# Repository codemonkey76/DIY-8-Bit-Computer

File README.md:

# DIY-8-Bit-Computer

Based off schematics and design of breadboard computer by Ben Eater, available in kit form at: https://eater.net/8bit/kits

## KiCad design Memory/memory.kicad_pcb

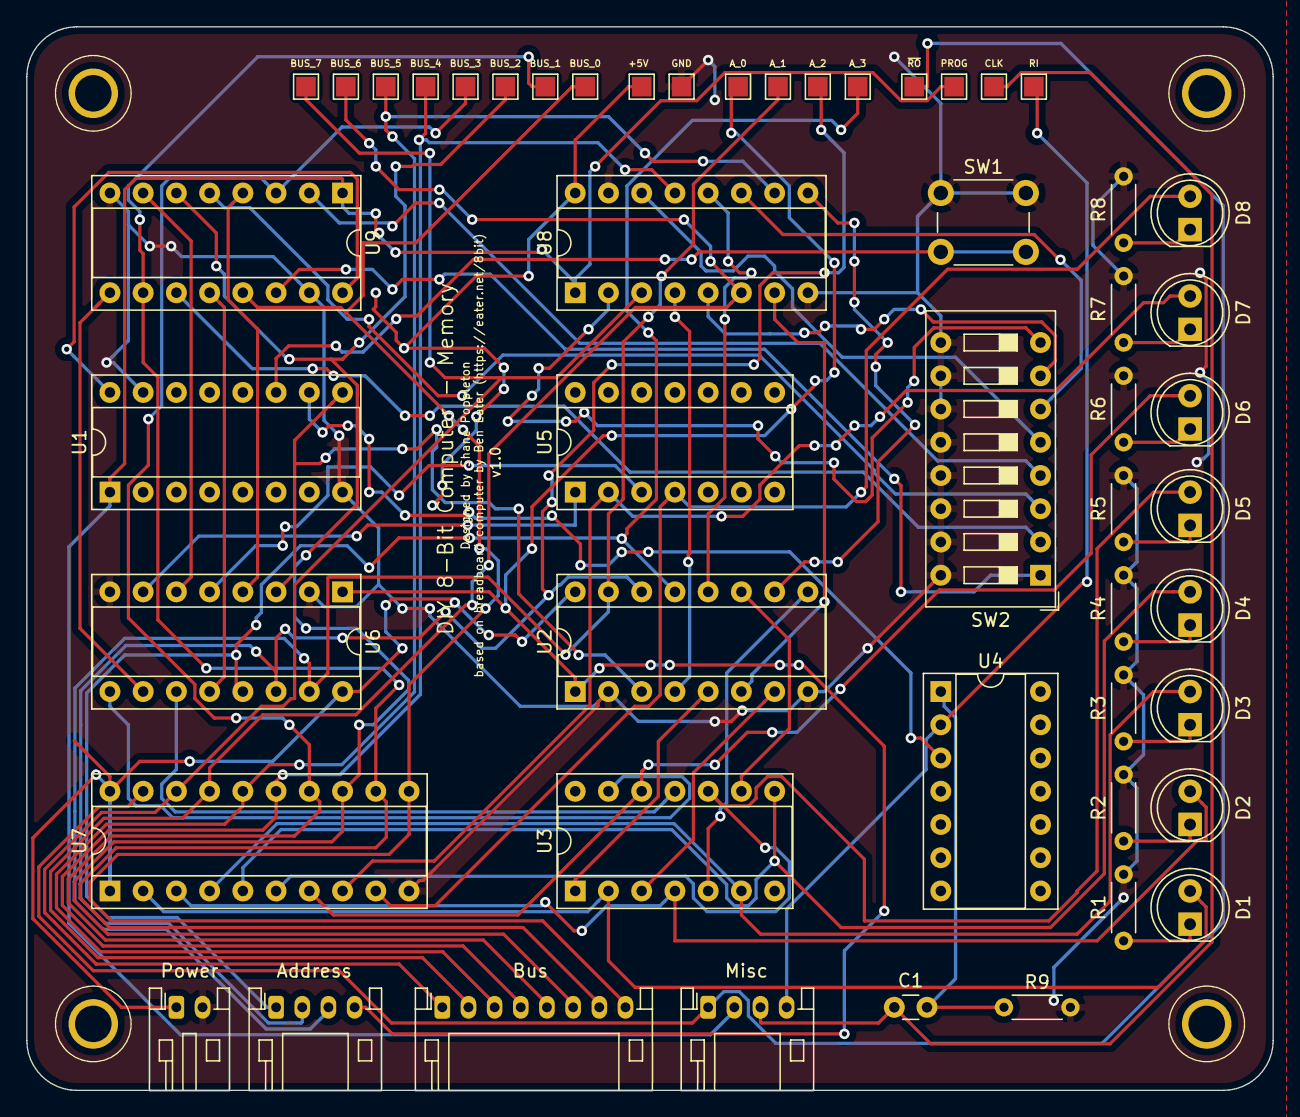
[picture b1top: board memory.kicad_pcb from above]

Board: 2 copper layers, 95.3 x 81.3 mm, 51 parts (0 on the bottom side), 62 nets.

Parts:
C1: 10nF; C_Disc_D3.0mm_W1.6mm_P2.50mm
D1, D2, D3, D4, D5, D6, D7, D8: LED; LED_D5.0mm
J1: Power; JST_PH_S2B-PH-K_1x02_P2.00mm_Horizontal
J2: Misc; JST_PH_S4B-PH-K_1x04_P2.00mm_Horizontal
J3: Address; JST_PH_S4B-PH-K_1x04_P2.00mm_Horizontal
J4: Bus; JST_PH_S8B-PH-K_1x08_P2.00mm_Horizontal
R1, R2, R3, R4, R5, R6, R7, R8: 220R; R_Axial_DIN0204_L3.6mm_D1.6mm_P5.08mm_Horizontal
R9: 1K; R_Axial_DIN0204_L3.6mm_D1.6mm_P5.08mm_Horizontal
SW1: SW_Push; SW_PUSH_6mm_H5mm
SW2: SW_DIP_x08; SW_DIP_SPSTx08_Slide_9.78x22.5mm_W7.62mm_P2.54mm
TP1: +5V; TestPoint_Pad_1.5x1.5mm
TP2: ~RO~; TestPoint_Pad_1.5x1.5mm
TP3: GND; TestPoint_Pad_1.5x1.5mm
TP4: A_3; TestPoint_Pad_1.5x1.5mm
TP5: A_2; TestPoint_Pad_1.5x1.5mm
TP6: A_1; TestPoint_Pad_1.5x1.5mm
TP7: RI; TestPoint_Pad_1.5x1.5mm
TP8: A_0; TestPoint_Pad_1.5x1.5mm
TP9: CLK; TestPoint_Pad_1.5x1.5mm
TP10: PROG; TestPoint_Pad_1.5x1.5mm
TP11: BUS_7; TestPoint_Pad_1.5x1.5mm
TP12: BUS_6; TestPoint_Pad_1.5x1.5mm
TP13: BUS_5; TestPoint_Pad_1.5x1.5mm
TP14: BUS_4; TestPoint_Pad_1.5x1.5mm
TP15: BUS_3; TestPoint_Pad_1.5x1.5mm
TP16: BUS_2; TestPoint_Pad_1.5x1.5mm
TP17: BUS_1; TestPoint_Pad_1.5x1.5mm
TP18: BUS_0; TestPoint_Pad_1.5x1.5mm
U1, U8, U9: 74LS157; DIP-16_W7.62mm_Socket
U2, U6: 74LS189; DIP-16_W7.62mm_Socket
U3, U5: 74LS04; DIP-14_W7.62mm_Socket
U4: 74LS00; DIP-14_W7.62mm_Socket
U7: 74LS245; DIP-20_W7.62mm_Socket

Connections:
+5V: J1.1, TP1.1, U1.16, U2.16, U6.16, U7.1, U7.20, U8.16, U9.16
/A0: J3.4, TP8.1, U2.1, U6.1
/A1: J3.3, TP6.1, U2.15, U6.15
/A2: J3.2, TP5.1, U2.14, U6.14
/A3: J3.1, TP4.1, U2.13, U6.13
/BUS_0: J4.8, TP18.1, U7.11, U9.13
/BUS_1: J4.7, TP17.1, U7.12, U9.10
/BUS_2: J4.6, TP16.1, U7.13, U9.6
/BUS_3: J4.5, TP15.1, U7.14, U9.3
/BUS_4: J4.4, TP14.1, U7.15, U8.13
/BUS_5: J4.3, TP13.1, U7.16, U8.10
/BUS_6: J4.2, TP12.1, U7.17, U8.6
/BUS_7: J4.1, TP11.1, U7.18, U8.3
/CLK: C1.1, J2.3, TP9.1
/PROG: J2.2, TP10.1, U1.1, U8.1, U9.1
/RI: J2.4, TP7.1, U4.2
/~RO~: J2.1, TP2.1, U7.19
GND: J1.2, R1.2, R2.2, R3.2, R4.2, R5.2, R6.2, R7.2, R8.2, R9.2, SW1.1, SW2.9, SW2.10, SW2.11, SW2.12, SW2.13, SW2.14, SW2.15, SW2.16, TP3.1, U1.8, U1.15, U2.2, U2.8, U6.2, U6.8, U7.10, U8.8, U8.15, U9.8, U9.15
unnamed: C1.2, R9.1, U4.1
unnamed: D1.1, R1.1
unnamed: D1.2, U3.2, U7.2
unnamed: D2.1, R2.1
unnamed: D2.2, U3.4, U7.3
unnamed: D3.1, R3.1
unnamed: D3.2, U3.6, U7.4
unnamed: D4.1, R4.1
unnamed: D4.2, U3.8, U7.5
unnamed: D5.1, R5.1
unnamed: D5.2, U3.10, U7.6
unnamed: D6.1, R6.1
unnamed: D6.2, U3.12, U7.7
unnamed: D7.1, R7.1
unnamed: D7.2, U5.2, U7.8
unnamed: D8.1, R8.1
unnamed: D8.2, U5.4, U7.9
unnamed: SW1.2, U1.11
unnamed: SW2.1, U9.14
unnamed: SW2.2, U9.11
unnamed: SW2.3, U9.5
unnamed: SW2.4, U9.2
unnamed: SW2.5, U8.14
unnamed: SW2.6, U8.11
unnamed: SW2.7, U8.5
unnamed: SW2.8, U8.2
unnamed: U1.9, U2.3, U6.3
unnamed: U1.10, U4.3
unnamed: U2.4, U8.4
unnamed: U2.5, U3.1
unnamed: U2.6, U8.7
unnamed: U2.7, U3.3
unnamed: U2.9, U3.5
unnamed: U2.10, U8.9
unnamed: U2.11, U3.9
unnamed: U2.12, U8.12
unnamed: U3.11, U6.11
unnamed: U3.13, U6.9
unnamed: U5.1, U6.7
unnamed: U5.3, U6.5
unnamed: U6.4, U9.4
unnamed: U6.6, U9.7
unnamed: U6.10, U9.9
unnamed: U6.12, U9.12

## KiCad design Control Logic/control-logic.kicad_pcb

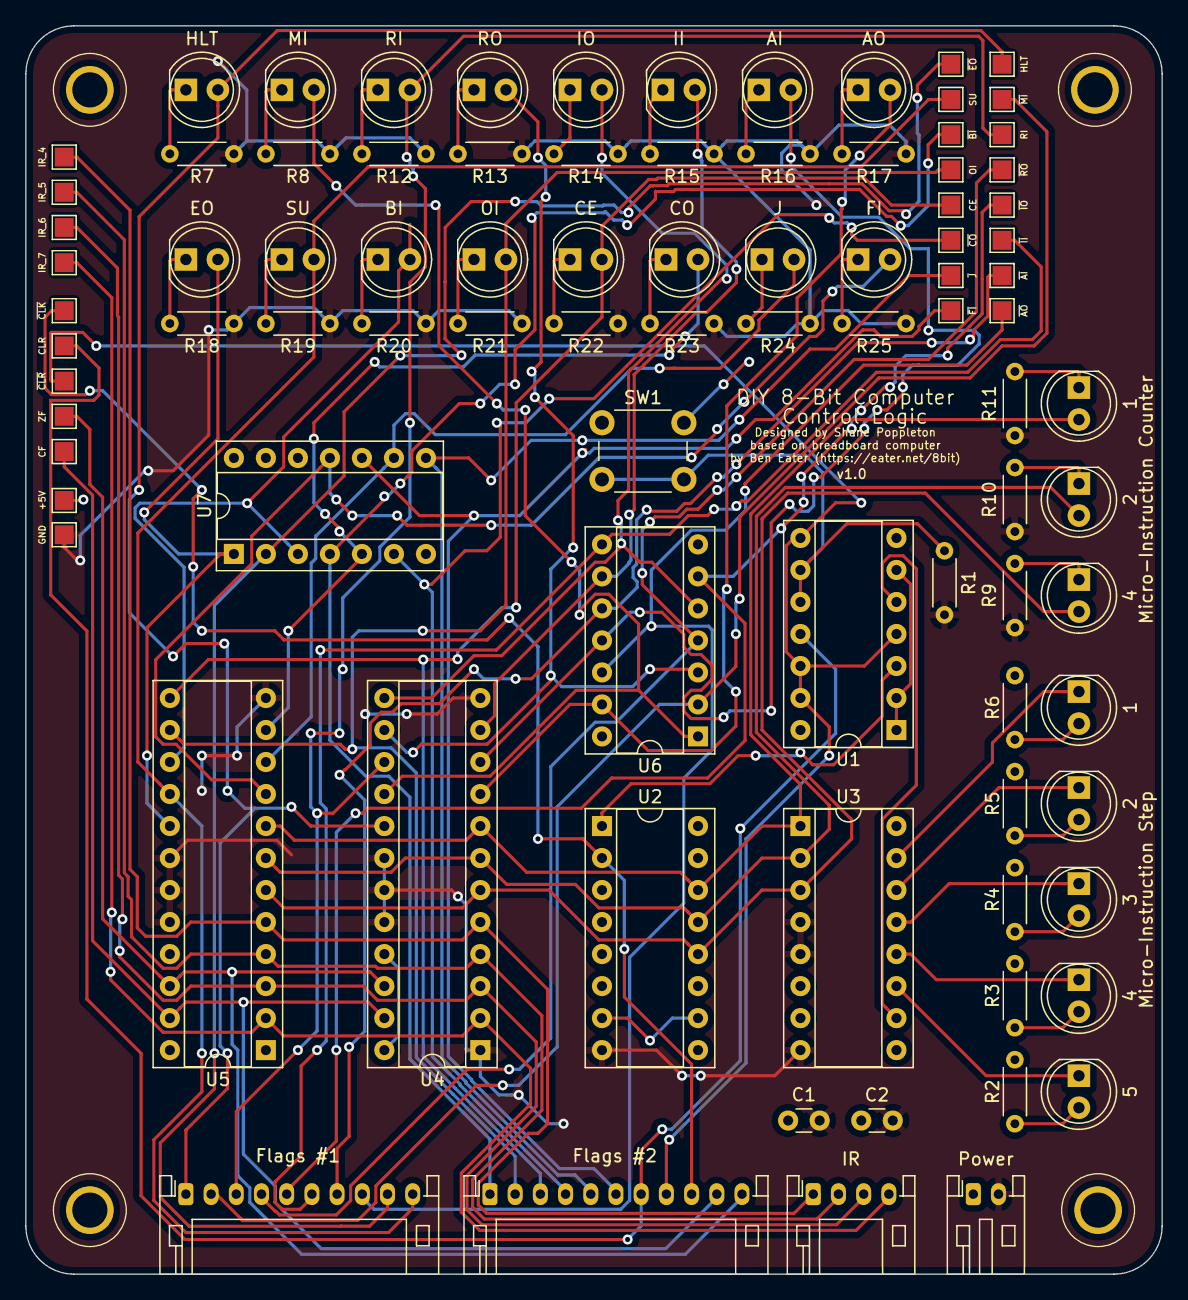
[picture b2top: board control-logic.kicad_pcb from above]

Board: 2 copper layers, 90.2 x 99.1 mm, 90 parts (0 on the bottom side), 74 nets.

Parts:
C1, C2: 100nF; C_Disc_D3.0mm_W1.6mm_P2.50mm
D1: 5; LED_D5.0mm
D2, D10: 4; LED_D5.0mm
D3: 3; LED_D5.0mm
D4, D11: 2; LED_D5.0mm
D5, D12: 1; LED_D5.0mm
D6: HLT; LED_D5.0mm
D7: MI; LED_D5.0mm
D8: RI; LED_D5.0mm
D9: RO; LED_D5.0mm
D13: IO; LED_D5.0mm
D14: II; LED_D5.0mm
D15: AI; LED_D5.0mm
D16: AO; LED_D5.0mm
D17: EO; LED_D5.0mm
D18: SU; LED_D5.0mm
D19: BI; LED_D5.0mm
D20: OI; LED_D5.0mm
D21: CE; LED_D5.0mm
D22: CO; LED_D5.0mm
D23: J; LED_D5.0mm
D24: FI; LED_D5.0mm
J1: Power; JST_PH_S2B-PH-K_1x02_P2.00mm_Horizontal
J2: IR; JST_PH_S4B-PH-K_1x04_P2.00mm_Horizontal
J3: Flags #2; JST_PH_S11B-PH-K_1x11_P2.00mm_Horizontal
J4: Flags #1; JST_PH_S10B-PH-K_1x10_P2.00mm_Horizontal
R1: 1K; R_Axial_DIN0204_L3.6mm_D1.6mm_P5.08mm_Horizontal
R2, R3, R4, R5, R6, R7, R8, R9, R10, R11, R12, R13, R14, R15, R16, R17, R18, R19, R20, R21, R22, R23, R24, R25: 220R; R_Axial_DIN0204_L3.6mm_D1.6mm_P5.08mm_Horizontal
SW1: SW_Push; SW_PUSH_6mm_H5mm
TP1: +5V; TestPoint_Pad_1.5x1.5mm
TP2: GND; TestPoint_Pad_1.5x1.5mm
TP3: ~CLR~; TestPoint_Pad_1.5x1.5mm
TP4: CLR; TestPoint_Pad_1.5x1.5mm
TP5: ~CLK~; TestPoint_Pad_1.5x1.5mm
TP6: IR_4; TestPoint_Pad_1.5x1.5mm
TP7: IR_5; TestPoint_Pad_1.5x1.5mm
TP8: IR_6; TestPoint_Pad_1.5x1.5mm
TP9: IR_7; TestPoint_Pad_1.5x1.5mm
TP10: CF; TestPoint_Pad_1.5x1.5mm
TP11: ZF; TestPoint_Pad_1.5x1.5mm
TP12: HLT; TestPoint_Pad_1.5x1.5mm
TP13: ~II~; TestPoint_Pad_1.5x1.5mm
TP14: ~MI~; TestPoint_Pad_1.5x1.5mm
TP15: ~AI~; TestPoint_Pad_1.5x1.5mm
TP16: RI; TestPoint_Pad_1.5x1.5mm
TP17: ~AO~; TestPoint_Pad_1.5x1.5mm
TP18: ~RO~; TestPoint_Pad_1.5x1.5mm
TP19: ~IO~; TestPoint_Pad_1.5x1.5mm
TP20: ~EO~; TestPoint_Pad_1.5x1.5mm
TP21: OI; TestPoint_Pad_1.5x1.5mm
TP22: ~CO~; TestPoint_Pad_1.5x1.5mm
TP23: SU; TestPoint_Pad_1.5x1.5mm
TP24: ~J~; TestPoint_Pad_1.5x1.5mm
TP25: CE; TestPoint_Pad_1.5x1.5mm
TP26: ~FI~; TestPoint_Pad_1.5x1.5mm
TP27: ~BI~; TestPoint_Pad_1.5x1.5mm
U1: 74LS00; DIP-14_W7.62mm_Socket
U2: 74LS161; DIP-16_W7.62mm_Socket
U3: 74LS138; DIP-16_W7.62mm_Socket
U4, U5: 24C16; DIP-24_W7.62mm_Socket
U6, U7: 74LS04; DIP-14_W7.62mm_Socket

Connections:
+5V: C1.1, C2.1, J1.1, R2.1, R3.1, R4.1, R5.1, R6.1, SW1.1, TP1.1, U2.7, U2.9, U2.10, U2.16, U3.6, U3.16, U4.21, U4.24, U5.1, U5.21, U5.24
/CE: D21.2, J3.3, TP25.1, U5.13
/HLT: D6.2, J4.1, TP12.1, U4.17
/IR_4: J2.1, TP6.1, U4.5, U5.5
/IR_5: J2.2, TP7.1, U4.4, U5.4
/IR_6: J2.3, TP8.1, U4.3, U5.3
/IR_7: J2.4, TP9.1, U4.2, U5.2
/OI: D20.2, J3.2, TP21.1, U5.14
/RI: D8.2, J4.3, TP16.1, U4.15
/SU: D18.2, J4.10, TP23.1, U5.16
/~AI~: J4.7, TP15.1, U6.10
/~AO~: J4.8, TP17.1, U6.12
/~BI~: J3.1, TP27.1, U7.4
/~CO~: J3.4, TP22.1, U7.6
/~EO~: J4.9, TP20.1, U7.2
/~FI~: J3.6, TP26.1, U7.10
/~II~: J4.6, TP13.1, U6.8
/~IO~: J4.5, TP19.1, U6.6
/~J~: J3.5, TP24.1, U7.8
/~MI~: J4.2, TP14.1, U6.2
/~RO~: J4.4, TP18.1, U6.4
CF: J3.10, TP10.1, U4.23, U5.23
CLR: J3.7, TP4.1, U1.11
GND: C1.2, C2.2, J1.2, R1.2, R7.2, R8.2, R9.2, R10.2, R11.2, R12.2, R13.2, R14.2, R15.2, R16.2, R17.2, R18.2, R19.2, R20.2, R21.2, R22.2, R23.2, R24.2, R25.2, TP2.1, U2.8, U3.4, U3.5, U3.8, U4.1, U4.12, U4.18, U4.19, U4.20, U5.12, U5.18, U5.19, U5.20
unnamed: D1.1, U3.11
unnamed: D1.2, R2.2
unnamed: D2.1, U3.12
unnamed: D2.2, R3.2
unnamed: D3.1, U3.13
unnamed: D3.2, R4.2
unnamed: D4.1, U3.14
unnamed: D4.2, R5.2
unnamed: D5.1, U3.15
unnamed: D5.2, R6.2
unnamed: D6.1, R7.1
unnamed: D7.1, R8.1
unnamed: D7.2, U4.16, U6.1
unnamed: D8.1, R12.1
unnamed: D9.1, R13.1
unnamed: D9.2, U4.14, U6.3
unnamed: D10.1, R9.1
unnamed: D10.2, U2.12, U3.3, U4.6, U5.6
unnamed: D11.1, R10.1
unnamed: D11.2, U2.13, U3.2, U4.7, U5.7
unnamed: D12.1, R11.1
unnamed: D12.2, U2.14, U3.1, U4.8, U5.8
unnamed: D13.1, R14.1
unnamed: D13.2, U4.13, U6.5
unnamed: D14.1, R15.1
unnamed: D14.2, U4.11, U6.9
unnamed: D15.1, R16.1
unnamed: D15.2, U4.10, U6.11
unnamed: D16.1, R17.1
unnamed: D16.2, U4.9, U6.13
unnamed: D17.1, R18.1
unnamed: D17.2, U5.17, U7.1
unnamed: D18.1, R19.1
unnamed: D19.1, R20.1
unnamed: D19.2, U5.15, U7.3
unnamed: D20.1, R21.1
unnamed: D21.1, R22.1
unnamed: D22.1, R23.1
unnamed: D22.2, U5.11, U7.5
unnamed: D23.1, R24.1
unnamed: D23.2, U5.10, U7.9
unnamed: D24.1, R25.1
unnamed: D24.2, U5.9, U7.11
unnamed: R1.1, SW1.2, U1.9, U1.10
unnamed: U1.1, U1.2, U1.6
unnamed: U1.3, U2.1
unnamed: U1.5, U3.10
ZF: J3.11, TP11.1, U4.22, U5.22
~CLK~: J3.9, TP5.1, U2.2
~CLR~: J3.8, TP3.1, U1.4, U1.8, U1.12, U1.13

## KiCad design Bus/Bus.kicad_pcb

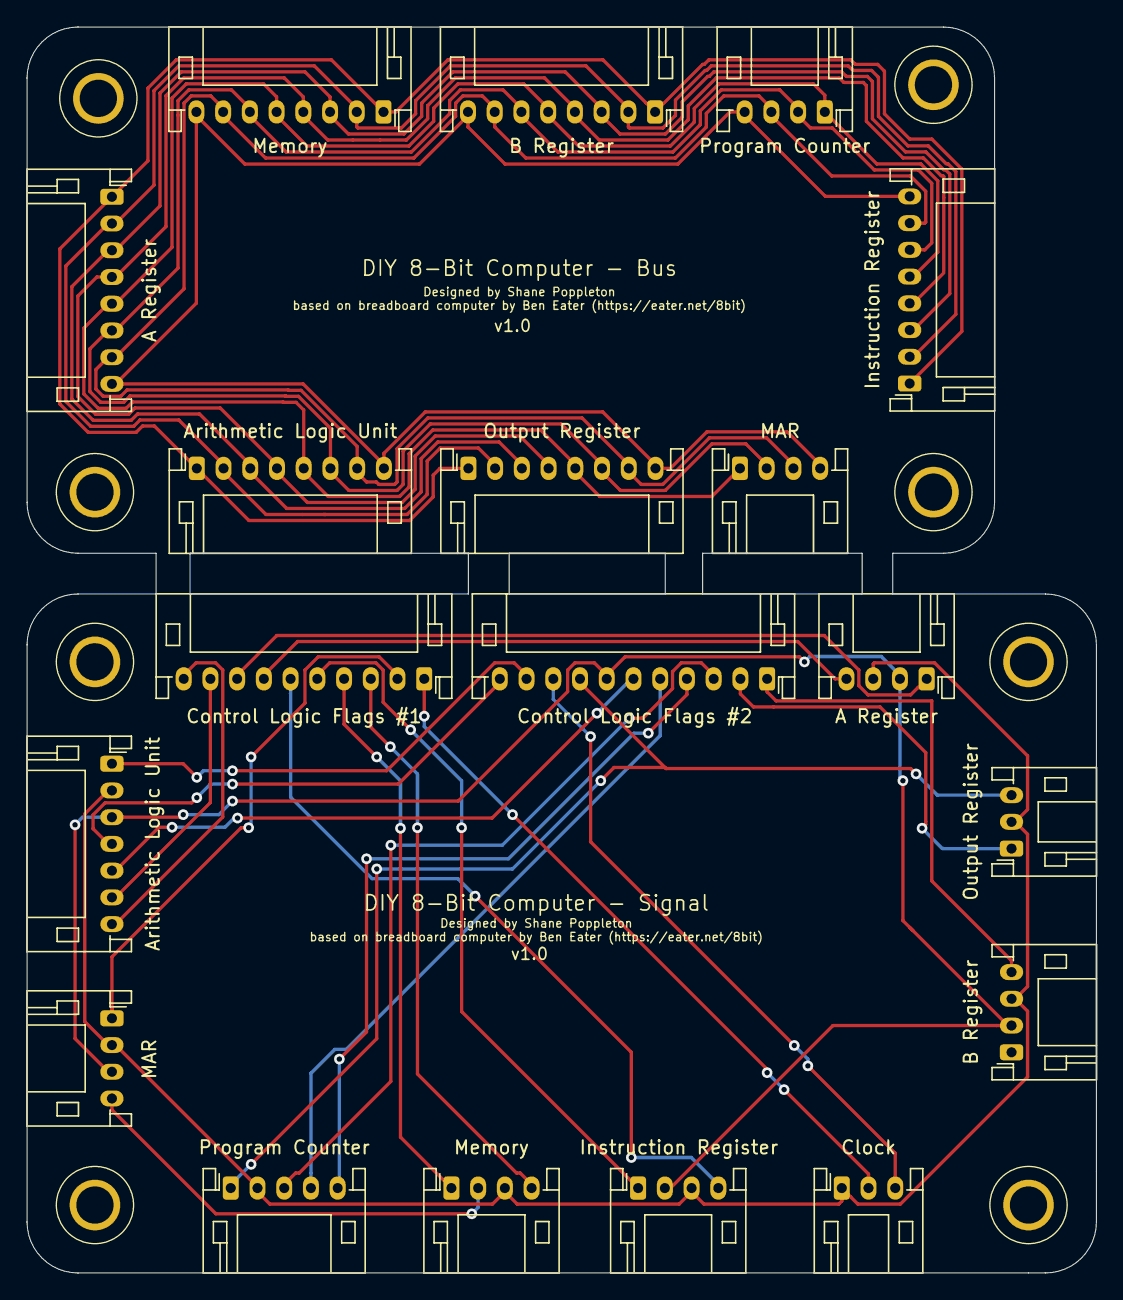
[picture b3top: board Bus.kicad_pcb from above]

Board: 2 copper layers, 80.0 x 93.2 mm, 19 parts (0 on the bottom side), 31 nets.

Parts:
J1: Clock; JST_PH_S3B-PH-K_1x03_P2.00mm_Horizontal
J2: Control Logic Flags #1; JST_PH_S10B-PH-K_1x10_P2.00mm_Horizontal
J3: Output Register; JST_PH_S8B-PH-K_1x08_P2.00mm_Horizontal
J5: Output Register; JST_PH_S3B-PH-K_1x03_P2.00mm_Horizontal
J8: Instruction Register; JST_PH_S8B-PH-K_1x08_P2.00mm_Horizontal
J9: Control Logic Flags #2; JST_PH_S11B-PH-K_1x11_P2.00mm_Horizontal
J12: Instruction Register; JST_PH_S4B-PH-K_1x04_P2.00mm_Horizontal
J13: A Register; JST_PH_S8B-PH-K_1x08_P2.00mm_Horizontal
J17: A Register; JST_PH_S4B-PH-K_1x04_P2.00mm_Horizontal
J18, J19: MAR; JST_PH_S4B-PH-K_1x04_P2.00mm_Horizontal
J20: B Register; JST_PH_S8B-PH-K_1x08_P2.00mm_Horizontal
J25: B Register; JST_PH_S4B-PH-K_1x04_P2.00mm_Horizontal
J26: Memory; JST_PH_S8B-PH-K_1x08_P2.00mm_Horizontal
J29: Memory; JST_PH_S4B-PH-K_1x04_P2.00mm_Horizontal
J30: Arithmetic Logic Unit; JST_PH_S7B-PH-K_1x07_P2.00mm_Horizontal
J31: Arithmetic Logic Unit; JST_PH_S8B-PH-K_1x08_P2.00mm_Horizontal
J32: Program Counter; JST_PH_S4B-PH-K_1x04_P2.00mm_Horizontal
J36: Program Counter; JST_PH_S5B-PH-K_1x05_P2.00mm_Horizontal

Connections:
BUS_0: J3.8, J8.8, J13.8, J19.4, J20.8, J26.8, J31.8, J32.4
BUS_1: J3.7, J8.7, J13.7, J19.3, J20.7, J26.7, J31.7, J32.3
BUS_2: J3.6, J8.6, J13.6, J19.2, J20.6, J26.6, J31.6, J32.2
BUS_3: J3.5, J8.5, J13.5, J19.1, J20.5, J26.5, J31.5, J32.1
BUS_4: J3.4, J8.4, J13.4, J20.4, J26.4, J31.4
BUS_5: J3.3, J8.3, J13.3, J20.3, J26.3, J31.3
BUS_6: J3.2, J8.2, J13.2, J20.2, J26.2, J31.2
BUS_7: J3.1, J8.1, J13.1, J20.1, J26.1, J31.1
CE: J9.3, J36.3
CF: J9.10, J30.1
CLK: J1.1, J5.2, J12.3, J17.3, J18.2, J25.3, J29.3, J30.2, J36.2
CLR: J9.7, J12.2, J17.2, J18.3, J25.2, J30.3
HLT: J1.2, J2.1
OI: J5.1, J9.2
PROG: J18.4, J29.2
RI: J2.3, J29.4
SU: J2.10, J30.7
ZF: J9.11, J30.4
~AI~: J2.7, J17.4
~AO~: J2.8, J17.1
~BI~: J9.1, J25.4
~CLK~: J1.3, J9.9
~CLR~: J5.3, J9.8, J36.1
~CO~: J9.4, J36.5
~EO~: J2.9, J30.6
~FI~: J9.6, J30.5
~II~: J2.6, J12.4
~IO~: J2.5, J12.1
~J~: J9.5, J36.4
~MI~: J2.2, J18.1
~RO~: J2.4, J29.1

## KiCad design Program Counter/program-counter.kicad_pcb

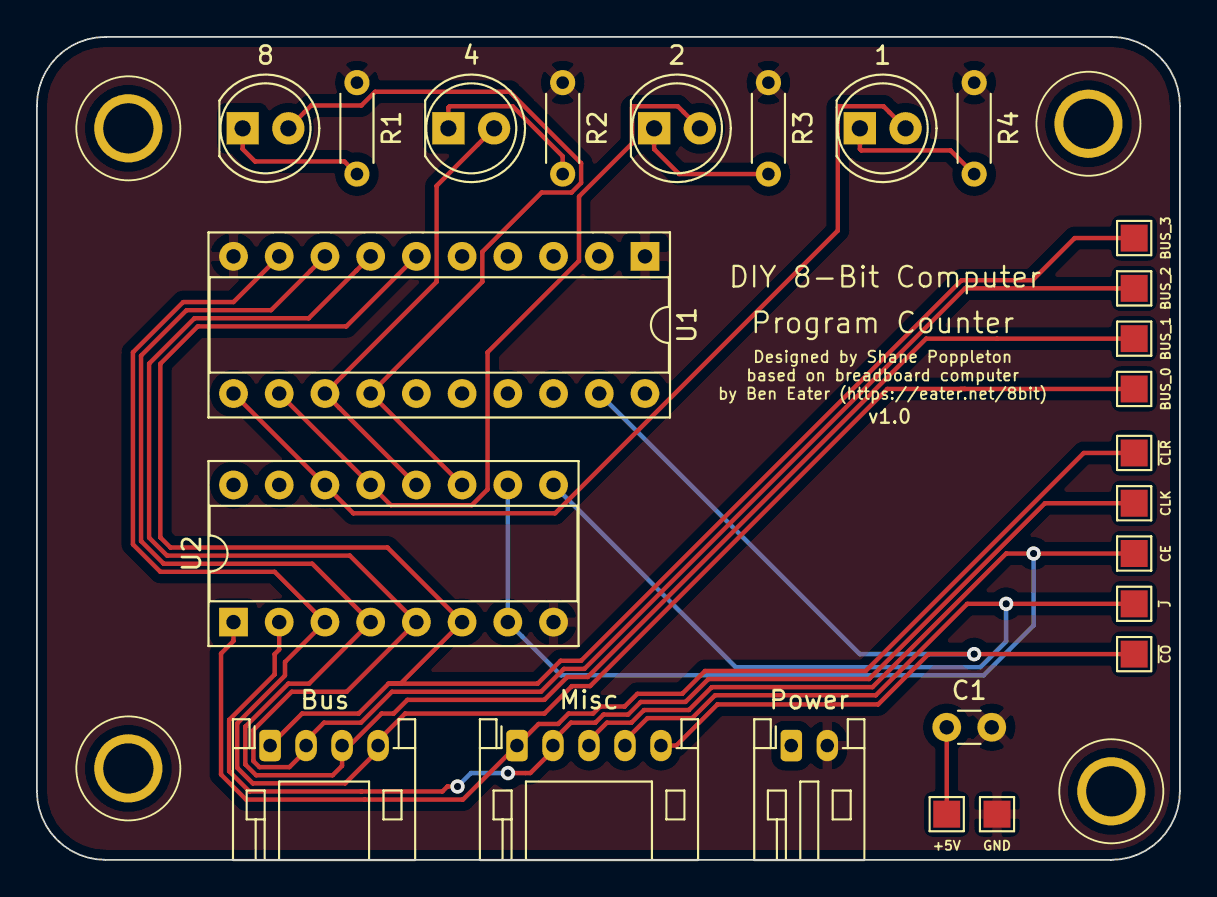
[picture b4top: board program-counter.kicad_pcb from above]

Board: 2 copper layers, 63.5 x 45.7 mm, 25 parts (0 on the bottom side), 19 nets.

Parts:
C1: 100nF; C_Disc_D3.0mm_W1.6mm_P2.50mm
D1: 8; LED_D5.0mm
D2: 4; LED_D5.0mm
D3: 2; LED_D5.0mm
D4: 1; LED_D5.0mm
J1: Misc; JST_PH_S5B-PH-K_1x05_P2.00mm_Horizontal
J2: Bus; JST_PH_S4B-PH-K_1x04_P2.00mm_Horizontal
J3: Power; JST_PH_S2B-PH-K_1x02_P2.00mm_Horizontal
R1, R2, R3, R4: 220R; R_Axial_DIN0204_L3.6mm_D1.6mm_P5.08mm_Horizontal
TP1: ~CO~; TestPoint_Pad_1.5x1.5mm
TP2: ~CLR~; TestPoint_Pad_1.5x1.5mm
TP3: CLK; TestPoint_Pad_1.5x1.5mm
TP4: ~J~; TestPoint_Pad_1.5x1.5mm
TP5: CE; TestPoint_Pad_1.5x1.5mm
TP6: BUS_2; TestPoint_Pad_1.5x1.5mm
TP7: BUS_0; TestPoint_Pad_1.5x1.5mm
TP8: BUS_1; TestPoint_Pad_1.5x1.5mm
TP9: BUS_3; TestPoint_Pad_1.5x1.5mm
TP10: GND; TestPoint_Pad_1.5x1.5mm
TP11: +5V; TestPoint_Pad_1.5x1.5mm
U1: 74LS245; DIP-20_W7.62mm_Socket
U2: 74LS161; DIP-16_W7.62mm_Socket

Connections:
+5V: C1.1, J3.1, TP11.1, U1.20, U2.16
/BUS_0: J2.4, TP7.1, U1.9, U2.3
/BUS_1: J2.3, TP8.1, U1.8, U2.4
/BUS_2: J2.2, TP6.1, U1.7, U2.5
/BUS_3: J2.1, TP9.1, U1.6, U2.6
/CE: J1.3, TP5.1, U2.7, U2.10
/CLK: J1.2, TP3.1, U2.2
/~CLR~: J1.1, TP2.1, U2.1
/~CO~: J1.5, TP1.1, U1.19
/~J~: J1.4, TP4.1, U2.9
GND: C1.2, J3.2, R1.1, R2.1, R3.1, R4.1, TP10.1, U1.1, U1.10, U2.8
unnamed: D1.1, R1.2
unnamed: D1.2, U1.14, U2.11
unnamed: D2.1, R2.2
unnamed: D2.2, U1.13, U2.12
unnamed: D3.1, R3.2
unnamed: D3.2, U1.12, U2.13
unnamed: D4.1, R4.2
unnamed: D4.2, U1.11, U2.14

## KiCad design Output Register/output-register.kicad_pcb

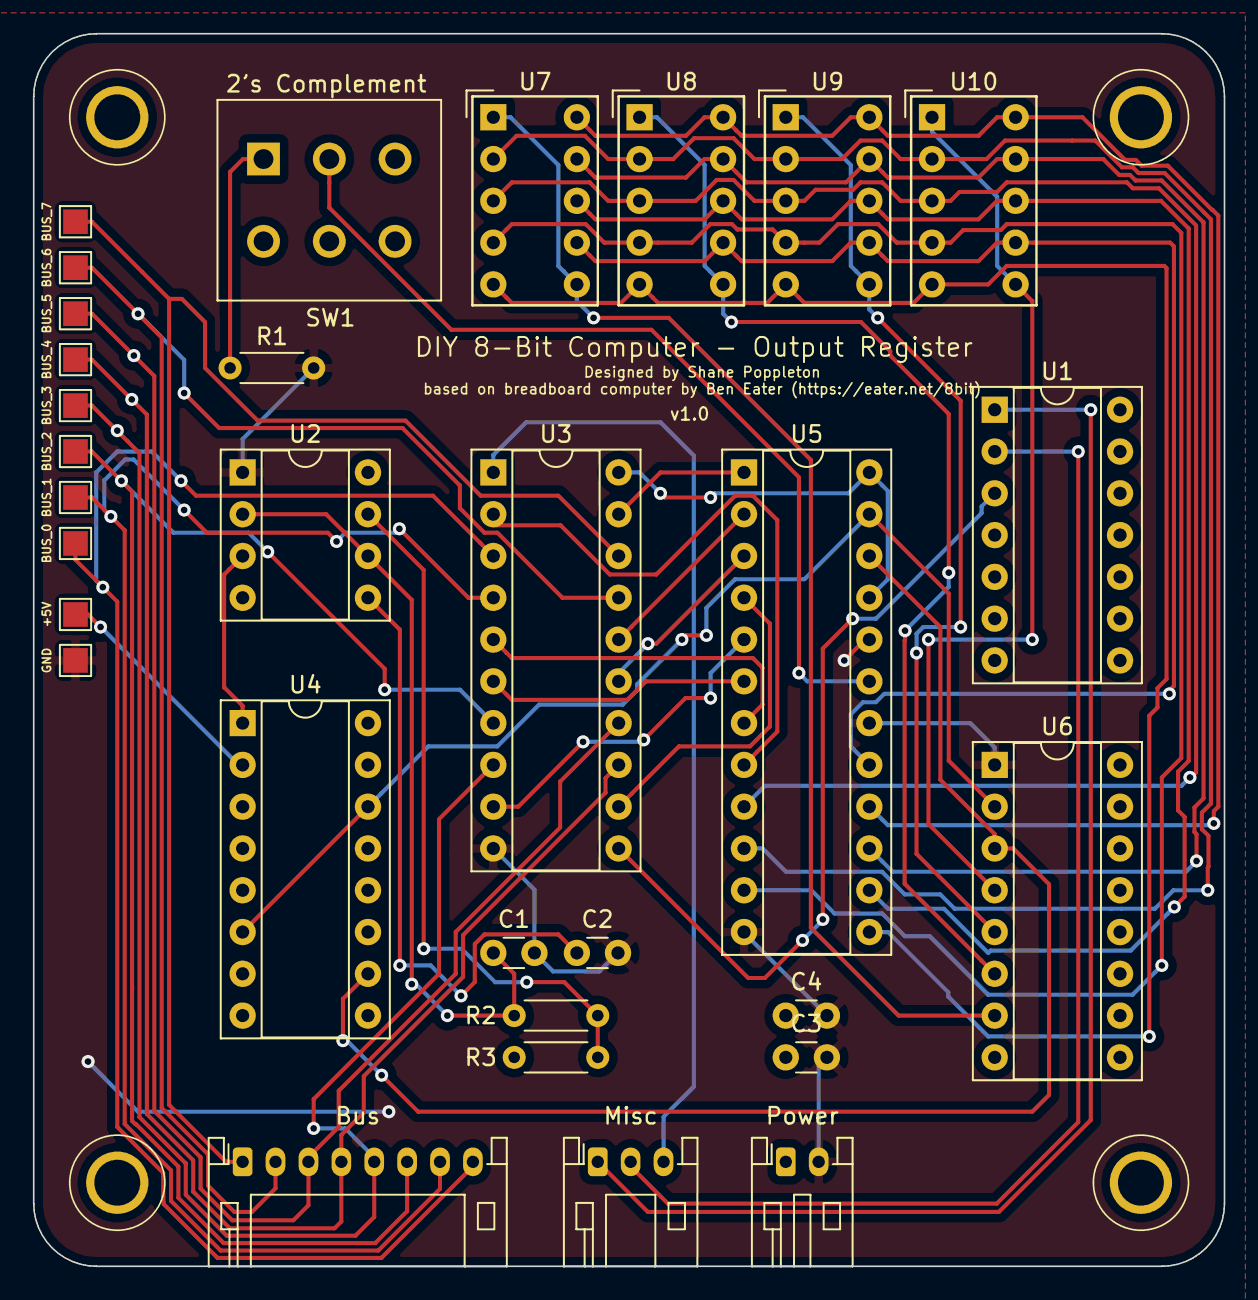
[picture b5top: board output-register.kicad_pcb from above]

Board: 2 copper layers, 72.4 x 74.9 mm, 31 parts (0 on the bottom side), 42 nets.

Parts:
C1, C2: 10nF; C_Disc_D3.0mm_W1.6mm_P2.50mm
C3, C4: 100nF; C_Disc_D3.0mm_W1.6mm_P2.50mm
J1: Bus; JST_PH_S8B-PH-K_1x08_P2.00mm_Horizontal
J2: Power; JST_PH_S2B-PH-K_1x02_P2.00mm_Horizontal
J3: Misc; JST_PH_S3B-PH-K_1x03_P2.00mm_Horizontal
R1: 10K; R_Axial_DIN0204_L3.6mm_D1.6mm_P5.08mm_Horizontal
R2: 100K; R_Axial_DIN0204_L3.6mm_D1.6mm_P5.08mm_Horizontal
R3: 1K; R_Axial_DIN0204_L3.6mm_D1.6mm_P5.08mm_Horizontal
SW1: Negative; SW_PUSH_E-Switch_FS5700DP_DPDT
TP1: BUS_0; TestPoint_Pad_1.5x1.5mm
TP2: BUS_1; TestPoint_Pad_1.5x1.5mm
TP3: BUS_2; TestPoint_Pad_1.5x1.5mm
TP4: BUS_3; TestPoint_Pad_1.5x1.5mm
TP5: BUS_4; TestPoint_Pad_1.5x1.5mm
TP6: BUS_5; TestPoint_Pad_1.5x1.5mm
TP7: BUS_6; TestPoint_Pad_1.5x1.5mm
TP8: BUS_7; TestPoint_Pad_1.5x1.5mm
TP9: +5V; TestPoint_Pad_1.5x1.5mm
TP10: GND; TestPoint_Pad_1.5x1.5mm
U1: 74LS08; DIP-14_W7.62mm_Socket
U2: LM555; DIP-8_W7.62mm_Socket
U3: 74LS273; DIP-20_W7.62mm_Socket
U4: 74LS76; DIP-16_W7.62mm_Socket
U5: 24C16; DIP-24_W7.62mm_Socket
U6: 74LS139; DIP-16_W7.62mm_Socket
U7, U8, U9, U10: HDSP-7403; HDSP-7401

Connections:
+5V: C3.1, C4.1, J2.1, R3.1, SW1.3, TP9.1, U2.8, U3.20, U4.2, U4.3, U4.4, U4.7, U4.8, U4.9, U4.12, U4.16, U5.21, U5.24
/BUS_0: J1.8, TP1.1, U3.3
/BUS_1: J1.7, TP2.1, U3.4
/BUS_2: J1.6, TP3.1, U3.7
/BUS_3: J1.5, TP4.1, U3.8
/BUS_4: J1.4, TP5.1, U3.13
/BUS_5: J1.3, TP6.1, U3.14
/BUS_6: J1.2, TP7.1, U3.17
/BUS_7: J1.1, TP8.1, U3.18
/CLK: J3.2, U1.2
/OI: J3.1, U1.1
/~CLR~: J3.3, U3.1
GND: C1.2, C2.2, C3.2, C4.2, J2.2, R1.2, TP10.1, U2.1, U3.10, U5.12, U5.18, U5.20, U6.1
unnamed: C1.1, R2.2, U2.2, U2.6
unnamed: C2.1, U2.5
unnamed: R1.1, SW1.1
unnamed: R2.1, R3.2, U2.7
unnamed: SW1.2, U5.19
unnamed: U1.3, U3.11
unnamed: U2.3, U4.1
unnamed: U3.2, U5.8
unnamed: U3.5, U5.7
unnamed: U3.6, U5.6
unnamed: U3.9, U5.5
unnamed: U3.12, U5.4
unnamed: U3.15, U5.3
unnamed: U3.16, U5.2
unnamed: U3.19, U5.1
unnamed: U4.10, U5.22, U6.3
unnamed: U4.6, U4.14, U5.23, U6.2
unnamed: U6.5, U9.1, U9.6
unnamed: U6.6, U8.1, U8.6
unnamed: U6.7, U7.1, U7.6
unnamed: U6.4, U10.1, U10.6
unnamed: U5.10, U7.2, U8.2, U9.2, U10.2
unnamed: U5.9, U7.3, U8.3, U9.3, U10.3
unnamed: U5.11, U7.4, U8.4, U9.4, U10.4
unnamed: U5.13, U7.5, U8.5, U9.5, U10.5
unnamed: U5.17, U7.7, U8.7, U9.7, U10.7
unnamed: U5.14, U7.8, U8.8, U9.8, U10.8
unnamed: U5.15, U7.9, U8.9, U9.9, U10.9
unnamed: U5.16, U7.10, U8.10, U9.10, U10.10

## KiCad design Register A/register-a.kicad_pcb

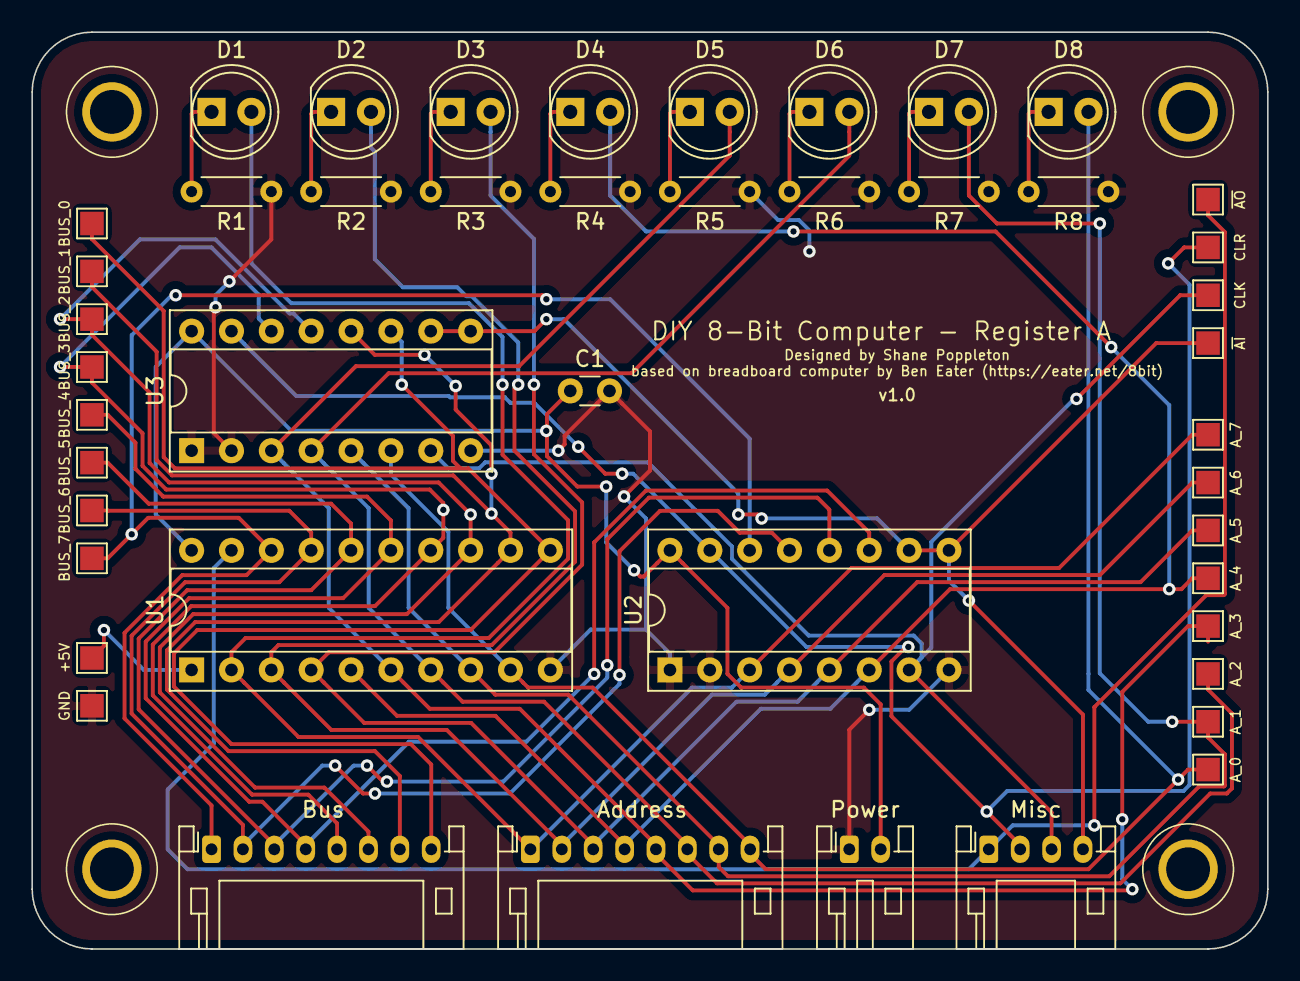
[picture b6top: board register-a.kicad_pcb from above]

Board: 2 copper layers, 78.7 x 58.4 mm, 46 parts (0 on the bottom side), 30 nets.

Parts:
C1: 100nF; C_Disc_D3.0mm_W1.6mm_P2.50mm
D1, D2, D3, D4, D5, D6, D7, D8: LED; LED_D5.0mm
J1: Bus; JST_PH_S8B-PH-K_1x08_P2.00mm_Horizontal
J2: Address; JST_PH_S8B-PH-K_1x08_P2.00mm_Horizontal
J3: Misc; JST_PH_S4B-PH-K_1x04_P2.00mm_Horizontal
J4: Power; JST_PH_S2B-PH-K_1x02_P2.00mm_Horizontal
R1, R2, R3, R4, R5, R6, R7, R8: 220R; R_Axial_DIN0204_L3.6mm_D1.6mm_P5.08mm_Horizontal
TP1: BUS_7; TestPoint_Pad_1.5x1.5mm
TP2: BUS_6; TestPoint_Pad_1.5x1.5mm
TP3: BUS_5; TestPoint_Pad_1.5x1.5mm
TP4: BUS_4; TestPoint_Pad_1.5x1.5mm
TP5: BUS_3; TestPoint_Pad_1.5x1.5mm
TP6: BUS_2; TestPoint_Pad_1.5x1.5mm
TP7: BUS_1; TestPoint_Pad_1.5x1.5mm
TP8: BUS_0; TestPoint_Pad_1.5x1.5mm
TP9: A_7; TestPoint_Pad_1.5x1.5mm
TP10: A_6; TestPoint_Pad_1.5x1.5mm
TP11: A_5; TestPoint_Pad_1.5x1.5mm
TP12: A_4; TestPoint_Pad_1.5x1.5mm
TP13: A_3; TestPoint_Pad_1.5x1.5mm
TP14: A_2; TestPoint_Pad_1.5x1.5mm
TP15: A_1; TestPoint_Pad_1.5x1.5mm
TP16: A_0; TestPoint_Pad_1.5x1.5mm
TP17: ~AI~; TestPoint_Pad_1.5x1.5mm
TP18: CLK; TestPoint_Pad_1.5x1.5mm
TP19: CLR; TestPoint_Pad_1.5x1.5mm
TP20: ~AO~; TestPoint_Pad_1.5x1.5mm
TP21: +5V; TestPoint_Pad_1.5x1.5mm
TP22: GND; TestPoint_Pad_1.5x1.5mm
U1: 74LS245; DIP-20_W7.62mm_Socket
U2, U3: 74LS173; DIP-16_W7.62mm_Socket

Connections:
+5V: C1.1, J4.2, TP21.1, U1.1, U1.20, U2.16, U3.16
/A_0: D8.2, J2.8, TP16.1, U1.9, U3.6
/A_1: D7.2, J2.7, TP15.1, U1.8, U3.5
/A_2: D6.2, J2.6, TP14.1, U1.7, U3.4
/A_3: D5.2, J2.5, TP13.1, U1.6, U3.3
/A_4: D4.2, J2.4, TP12.1, U1.5, U2.6
/A_5: D3.2, J2.3, TP11.1, U1.4, U2.5
/A_6: D2.2, J2.2, TP10.1, U1.3, U2.4
/A_7: D1.2, J2.1, TP9.1, U1.2, U2.3
/BUS_0: J1.8, TP8.1, U1.11, U3.11
/BUS_1: J1.7, TP7.1, U1.12, U3.12
/BUS_2: J1.6, TP6.1, U1.13, U3.13
/BUS_3: J1.5, TP5.1, U1.14, U3.14
/BUS_4: J1.4, TP4.1, U1.15, U2.11
/BUS_5: J1.3, TP3.1, U1.16, U2.12
/BUS_6: J1.2, TP2.1, U1.17, U2.13
/BUS_7: J1.1, TP1.1, U1.18, U2.14
/CLK: J3.3, TP18.1, U2.7, U3.7
/CLR: J3.2, TP19.1, U2.15, U3.15
/~AI~: J3.4, TP17.1, U2.9, U2.10, U3.9, U3.10
/~AO~: J3.1, TP20.1, U1.19
GND: C1.2, J4.1, R1.2, R2.2, R3.2, R4.2, R5.2, R6.2, R7.2, R8.2, TP22.1, U1.10, U2.1, U2.2, U2.8, U3.1, U3.2, U3.8
unnamed: D1.1, R1.1
unnamed: D2.1, R2.1
unnamed: D3.1, R3.1
unnamed: D4.1, R4.1
unnamed: D5.1, R5.1
unnamed: D6.1, R6.1
unnamed: D7.1, R7.1
unnamed: D8.1, R8.1

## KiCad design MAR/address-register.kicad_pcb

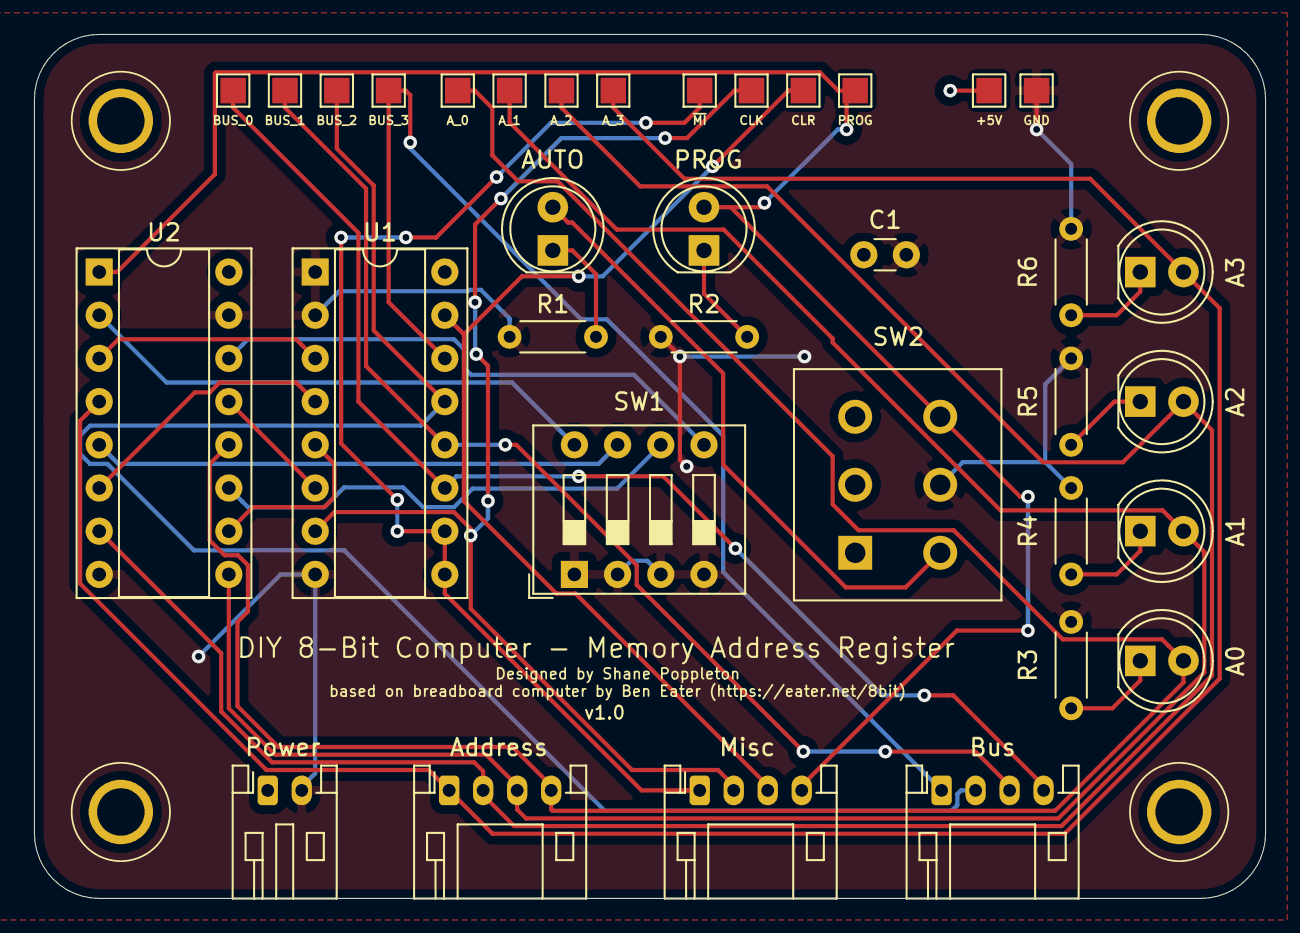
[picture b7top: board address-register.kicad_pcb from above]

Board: 2 copper layers, 72.4 x 50.8 mm, 35 parts (0 on the bottom side), 29 nets.

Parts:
C1: 100nF; C_Disc_D3.0mm_W1.6mm_P2.50mm
D1: AUTO; LED_D5.0mm
D2: PROG; LED_D5.0mm
D3: A0; LED_D5.0mm
D4: A1; LED_D5.0mm
D5: A2; LED_D5.0mm
D6: A3; LED_D5.0mm
J1: Power; JST_PH_S2B-PH-K_1x02_P2.00mm_Horizontal
J2: Bus; JST_PH_S4B-PH-K_1x04_P2.00mm_Horizontal
J3: Misc; JST_PH_S4B-PH-K_1x04_P2.00mm_Horizontal
J4: Address; JST_PH_S4B-PH-K_1x04_P2.00mm_Horizontal
R1, R2, R3, R4, R5, R6: 220R; R_Axial_DIN0204_L3.6mm_D1.6mm_P5.08mm_Horizontal
SW1: SW_DIP_x04; SW_DIP_SPSTx04_Slide_9.78x12.34mm_W7.62mm_P2.54mm
SW2: SW_DPDT_x2; SW_PUSH_E-Switch_FS5700DP_DPDT
TP1: BUS_0; TestPoint_Pad_1.5x1.5mm
TP2: BUS_1; TestPoint_Pad_1.5x1.5mm
TP3: ~MI~; TestPoint_Pad_1.5x1.5mm
TP4: CLK; TestPoint_Pad_1.5x1.5mm
TP5: BUS_2; TestPoint_Pad_1.5x1.5mm
TP6: CLR; TestPoint_Pad_1.5x1.5mm
TP7: BUS_3; TestPoint_Pad_1.5x1.5mm
TP8: PROG; TestPoint_Pad_1.5x1.5mm
TP9: GND; TestPoint_Pad_1.5x1.5mm
TP10: A_0; TestPoint_Pad_1.5x1.5mm
TP11: A_1; TestPoint_Pad_1.5x1.5mm
TP12: A_2; TestPoint_Pad_1.5x1.5mm
TP13: A_3; TestPoint_Pad_1.5x1.5mm
TP14: +5V; TestPoint_Pad_1.5x1.5mm
U1: 74LS173; DIP-16_W7.62mm_Socket
U2: 74LS157; DIP-16_W7.62mm_Socket

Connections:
+5V: C1.1, J1.1, TP14.1, U1.16, U2.16
/A0: D3.2, J4.4, TP10.1, U2.12
/A1: D4.2, J4.3, TP11.1, U2.9
/A2: D5.2, J4.2, TP12.1, U2.7
/A3: D6.2, J4.1, TP13.1, U2.4
/BUS_0: J2.4, TP1.1, U1.11
/BUS_1: J2.3, TP2.1, U1.12
/BUS_2: J2.2, TP5.1, U1.13
/BUS_3: J2.1, TP7.1, U1.14
/CLK: J3.2, TP4.1, U1.7
/CLR: J3.3, TP6.1, U1.15
/PROG: D2.2, J3.4, SW2.6, TP8.1, U2.1
/~MI~: J3.1, TP3.1, U1.9, U1.10
GND: C1.2, J1.2, R1.1, R2.1, R3.1, R4.1, R5.1, R6.1, SW1.1, SW1.2, SW1.3, SW1.4, SW2.5, TP9.1, U1.1, U1.2, U1.8, U2.8, U2.15
unnamed: D1.1, R1.2
unnamed: D1.2, SW2.4
unnamed: D2.1, R2.2
unnamed: D3.1, R3.2
unnamed: D4.1, R4.2
unnamed: D5.1, R5.2
unnamed: D6.1, R6.2
unnamed: SW1.5, U2.14
unnamed: SW1.6, U2.11
unnamed: SW1.7, U2.5
unnamed: SW1.8, U2.2
unnamed: U1.3, U2.3
unnamed: U1.4, U2.6
unnamed: U1.5, U2.10
unnamed: U1.6, U2.13
